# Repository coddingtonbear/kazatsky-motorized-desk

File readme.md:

# Kazatsky: DIY Motorized IKEA Desk

The project herein is everything I used for converting my manually-cranked [IKEA Skarsta Desk](https://www.ikea.com/us/en/p/skarsta-desk-sit-stand-white-s49084965/) into a motorized one using parts from a cheap [Harbor Freight 18v Drill Master Drill](https://www.harborfreight.com/18-Volt-38-in-Cordless-DrillDriver-Kit-With-Keyless-Chuck-21-Clutch-Settings-62873.html), a DIY Atmega328pb-based PCB, a [BTS7960 motor driver module](https://www.amazon.com/DEVMO-BTS7960B-Stepper-H-Bridge-Arduino/dp/B07SZ4T699/ref=sr_1_3?keywords=BTS7960+motor+driver&qid=1570931471&s=electronics&sr=1-3), a handful of 3D-printed parts, and miscellaneous hardware.

You can also find the 3d-printed parts on Thingiverse: https://www.thingiverse.com/thing:3912988

This is named after the traditional Russian folk dance called the "Kazatsky" because of the parallels that can be drawn between that dance's main movement and the comically fast speed at which this desk can be raised up and down when running the drill at full-bore.

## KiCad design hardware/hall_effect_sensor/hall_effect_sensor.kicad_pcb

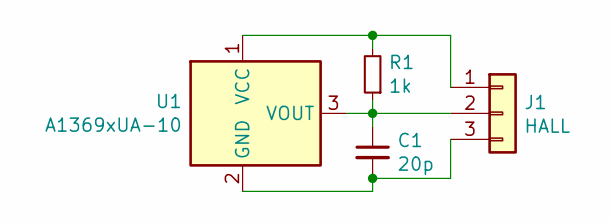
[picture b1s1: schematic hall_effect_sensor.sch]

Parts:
C1: 20p; 0805_Milling
J1: HALL; PinHeader_1x03_P2.54mm_Vertical
R1: 1k; 0805_Milling
U1: A1369xUA-10; Allegro_SIP-3

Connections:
unnamed: C1.1, J1.2, R1.1, U1.3 (VOUT)
unnamed: C1.2, J1.3, U1.2 (GND)
unnamed: J1.1, R1.2, U1.1 (VCC)

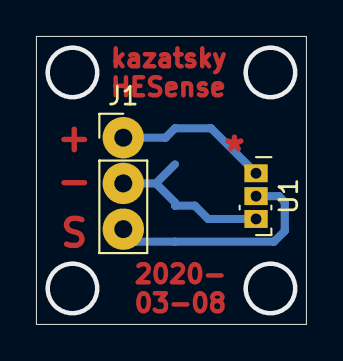
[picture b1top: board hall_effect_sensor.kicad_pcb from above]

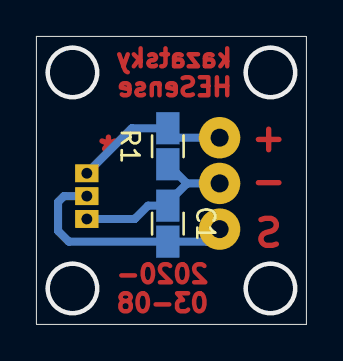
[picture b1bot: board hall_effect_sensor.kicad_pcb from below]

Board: 2 copper layers, 15.0 x 16.0 mm, 4 parts (2 on the bottom side), 3 nets.

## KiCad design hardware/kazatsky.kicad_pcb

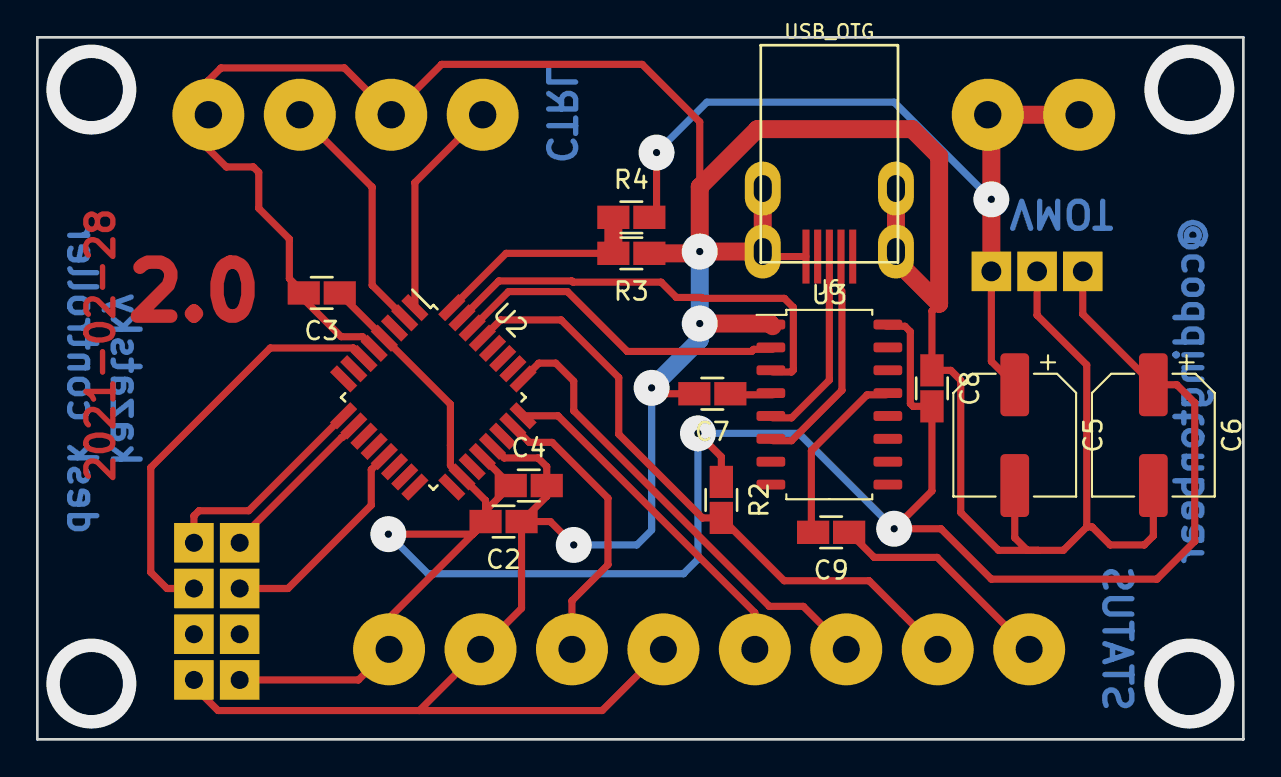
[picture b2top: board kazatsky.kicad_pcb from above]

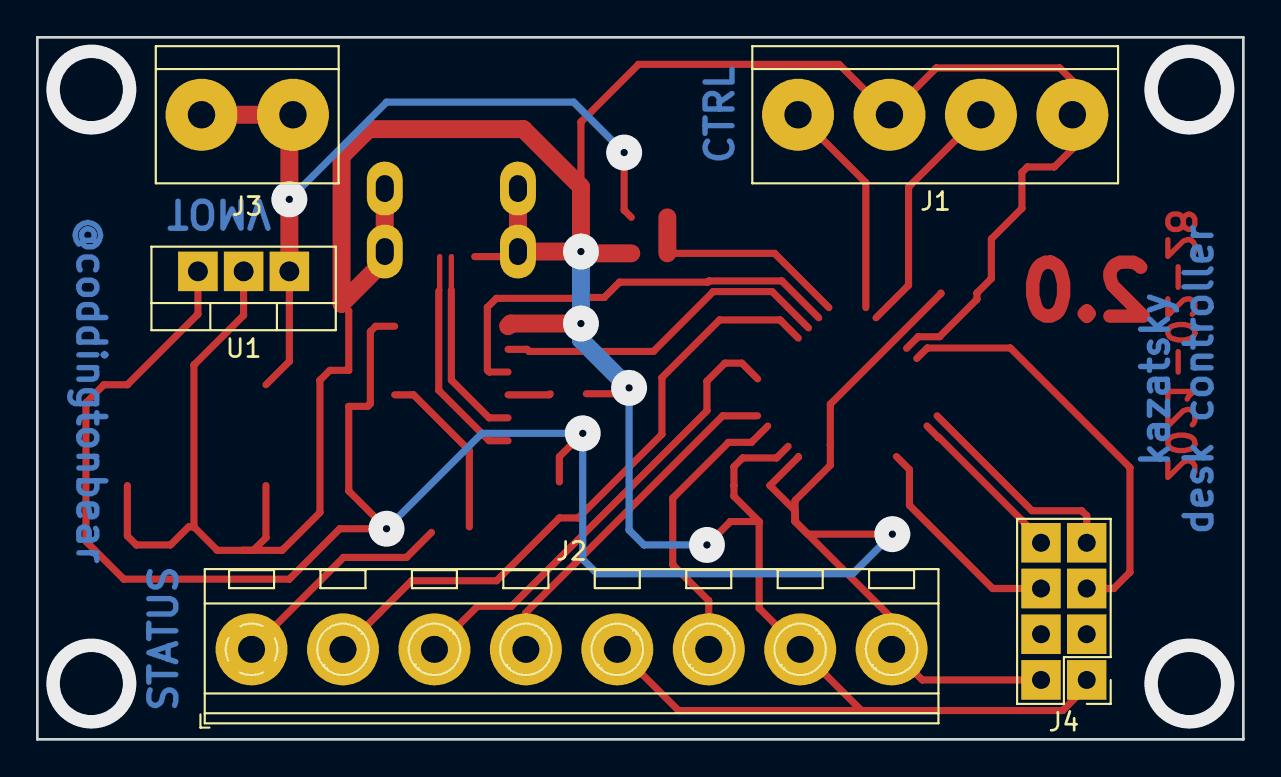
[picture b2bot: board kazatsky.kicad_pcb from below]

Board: 2 copper layers, 67.0 x 39.0 mm, 19 parts (5 on the bottom side), 21 nets.

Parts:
C2, C3, C4, C7, C8, C9: 0.1u; 0805_Milling
C5, C6: 100u; CP_Elec_6.3x5.4
J1: CTRL; TerminalBlock_bornier-4_P5.08mm
J2: HALL/LIMIT/RST; TerminalBlock_RND_205-00238_1x08_P5.08mm_Horizontal
J3: VMOT; TerminalBlock_bornier-2_P5.08mm
J4: MOTOR; PinHeader_2x04_P2.54mm_Vertical
J6: USB_OTG; UJ2-MIBH-4-SMT
R2: 100k; 0805_Milling
R3: 3.4k; 0805_Milling
R4: 10.2k; 0805_Milling
U1: L7805; TO-220-3_Vertical
U2: ATmega328PB-AU; TQFP-32_7x7mm_P0.8mm
U3: CH340B; SOIC-16_4.55x10.3mm_P1.27mm

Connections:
+5V: C2.2, C3.1, C4.1, C6.1, C8.2, J2.8, J4.2, R2.1, U1.3, U2.4, U2.18, U2.20, U3.16
+VDC: C5.1, J3.1, J3.2, R4.2, U1.1
/UD+: J6.3, U3.5
/UD-: J6.2, U3.6
CTRL_DOWN: J1.2, U2.2
CTRL_UP: J1.4, U2.1
GND: C2.1, C3.2, C4.2, C5.2, C6.2, C7.2, C8.1, J1.1, J1.3, J2.5, J2.7, J4.1, J6.5, J6.6, R3.1, U1.2, U2.5, U2.21, U3.1
HALL: J2.6, U2.23
L_EN: J4.5, U2.6
L_PWM: J4.7, U2.9
unnamed: C7.1, U3.4
unnamed: C9.2, U3.13
unnamed: J2.3, U2.25
RXD: U2.30, U3.2
R_EN: J4.6, U2.13
R_PWM: J4.8, U2.10
TXD: U2.31, U3.3
USB_RESET: J2.2, R2.2, U2.29
USB_RESET_DTR: C9.1, J2.1
VMOT: R3.2, R4.1, U2.32
~LIMIT: J2.4, U2.24

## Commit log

2019-10-08 Addinv v1 of the board design.
2019-10-08 Adding ADC pin for measuring input voltage.
2019-10-08 Adding name/date/etc to board.
2019-10-08 Minor gnd/5v layout changes.
2019-10-08 Adding gerbers and gcode.
2019-10-11 Adding firmware.
2019-10-11 Latest hardware version.
2019-10-12 Updating pins.
2019-10-12 Fully-working; including keeping track of position between resets & reading from hall effect sensor.
2019-10-13 Adding get_position and to_position serial commands.
2019-10-13 Add commands for resetting desk zero point, and getting current input voltage.
2019-10-13 Adding 3d-printable parts.
2019-10-13 Adding header file.
2019-10-13 Updating readme.
2019-10-13 Minor readme updates.
2019-10-14 Updating firmware to include mm-aware heights.
2020-07-05 Debounce hall effect sensor & button inputs; detect motor stall.
2021-03-01 Updating to v2.0 of the board.
2021-03-01 Adding extra capacitance.
2021-03-01 Updating board version/date.
2021-03-06 PCB v2.0.
2021-03-06 Updating software slightly.
2021-03-06 Use the motor to make a beeping noise at start, limit.
2021-03-09 Adding offboard hall effect sensor.
2021-03-09 Updating board to include mounting holes.
2021-03-09 Updating footprint for hall-effect sensor.
2021-03-12 Updating hall effect board slightly.
2021-03-14 Slowly ramp speed up/down when pressing/releasing buttons. Display current status on output. Add motor safety functionality for disabling motors in the event of a firmware problem.
2021-03-14 Removing motor stall detection; just rely on the limit switch, it's fine.
